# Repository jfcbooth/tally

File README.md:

# Tally
 
A battery-powered seven-segment display counter using a custom PCB. A counter like this can have many unique purposes and can be quickly modified to serve new purpose.

## Resetting the tally
To reset the counter to 0, press either button to wake the device from sleep, then press the small yellow button on the back of the PCB (labelled BTN).

All files necessary to build one for yourself are included in this repository.

<!-- START doctoc generated TOC please keep comment here to allow auto update -->
<!-- DON'T EDIT THIS SECTION, INSTEAD RE-RUN doctoc TO UPDATE -->

- [ATMEGA328 Software](#atmega328-software)
- [PCB](#pcb)
- [Case](#case)

<!-- END doctoc generated TOC please keep comment here to allow auto update -->

## ATMEGA328 Software
1.) Burn Fuses
 - Open arduino software and add the MiniCore library to your board manager:  
 Preferences->Additional Board Manager URLS->paste https://mcudude.github.io/MiniCore/package_MCUdude_MiniCore_index.json  
 - Tools->Board Manager->Search "minicore"->Install  
 - Upload asrduinoISP sketch from arduino software to an arduino uno.  
 - Connect to ATMEGA as shown here:  

| Configured with internal clock | Configured with external clock |
| ----------- | ----------- |
|  |  |

Arduino Flash Options:  
Board->Minicore->ATMEGA328P  
Clock->Internal 1Mhz  
BOD->1.8V  
EEPROM->EEPROM retained  
Compiler LTO->LTO disabled  
Variant->328P/328A  
Bootloader->No bootloader  
PORT-> select your COM port  
Programmer->Arduino as ISP  
Burn bootloader  

Trying configuring the ATMEGA328 with the internal clock first, but if the code doesn't upload, it was probably configured to use an external 16Mhz clock from the factory. You will need a 16Mhz clock which can be de-soldered from an old/dead arduino and 2 22nF capacitors. After burning the bootloader (which sets the fuses), you can remove the crystal and won't need it when uploading sketches from now on. If the code still doesn't upload, make sure all grounds are connected and the supplied voltage is >3V.

2.) Upload Sketch  
 - Open arduino sketch in src  
 - Upload as programmer  (shift click on upload button)

3.) Install ATMEGA328P into PCB  (Note the orientation)

## PCB
| Hardware | Quantity | Purchase location |
| -----------  | -----------  | -----------  |
| ATMEGA328P-PU | 1 | [mouser](https://www.mouser.com/ProductDetail/556-ATMEGA328P-PU) |
| TDCR1050M | 1 | [mouser](https://www.mouser.com/ProductDetail/78-TDCR1050M) |
| C0402C103K5RAC7411 | 4 | [mouser](https://www.mouser.com/ProductDetail/80-C0402C103K5R7411) |
| TPS7A0520PDBZR | 1 | [mouser](https://www.mouser.com/ProductDetail/595-TPS7A0520PDBZR) |
| CRCW08054K70FKEAC | 6 | [mouser](https://www.mouser.com/ProductDetail/71-CRCW08054K70FKEAC) |
| 865080440002 | 2 | [mouser](https://www.mouser.com/ProductDetail/710-865080440002) |
| PTS526 SK08 SMTR2 LFS | 1 | [mouser](https://www.mouser.com/ProductDetail/611-PTS526SK08SMTR2L) |
| 2468 | 1 | [mouser](https://www.mouser.com/ProductDetail/534-2468) |
| Cherry MX Switch Blue | 2 | [amazon](https://www.amazon.com/Cherry-switches-MX1AG1NN-Mechanical-Keyboard/dp/B07RQTNS58/ref=sr_1_3?dchild=1&keywords=cherry+mx+blue+switch&qid=1633447512&sr=8-3) |

I ordered my PCB's through JLCPCB.  
If ordering through them, you can just upload the tally_cam_data.zip zip file in the schematics folder to their website.  
I was supposed to be able to make this design at my university, but none of my professors know how to use the lab eqipment, so I had to order them through a 3rd party. Go Raiders!  

1.) Solder components to PCB (except cherry mx switches)  
2.) Install battery box first by sliding it into place  
3.) Screw PCB into place  
4.) Install Cherry MX switches and solder them to the board  

## Case
For the case, orient it standing tall with the cherry mx switches toward the top.  
It needs printed with a .2mm nozzle for the front lettering to print properly.  
The case is 3d printed, for the back plate, print it laying flat.

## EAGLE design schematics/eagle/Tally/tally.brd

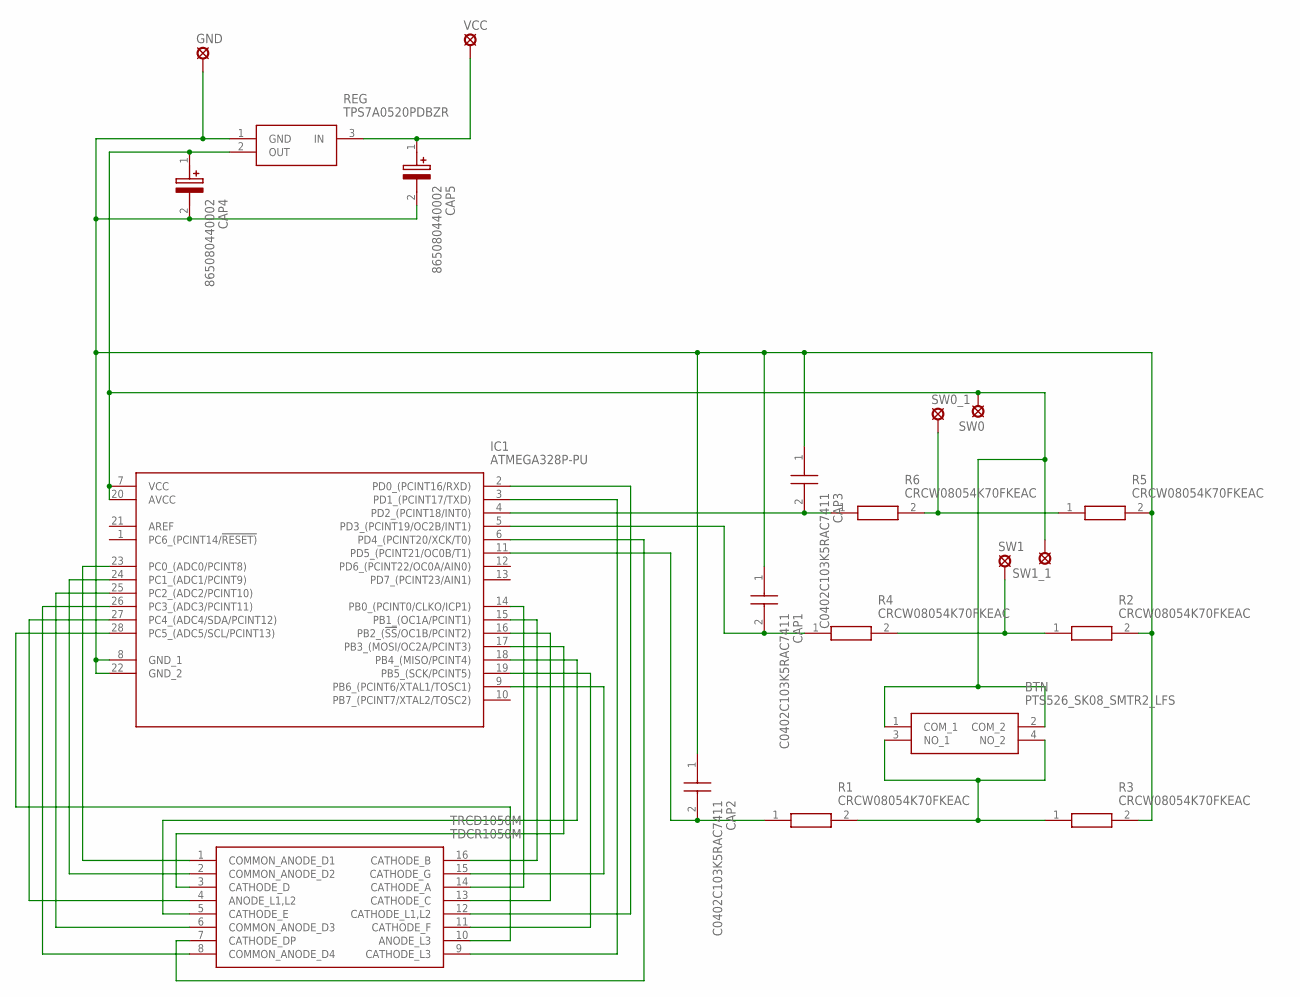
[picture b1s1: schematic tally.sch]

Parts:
BTN: PTS526_SK08_SMTR2_LFS; PTS526SKG15SMTR2LFS
CAP1, CAP2, CAP3: C0402C103K5RAC7411; CAPC1005X55N
CAP4, CAP5: 865080440002; CAPAE400X550N
GND: LSP11
IC1: ATMEGA328P-PU; DIP794W53P254L3467H457Q28N
R1, R2, R3, R4, R5, R6: CRCW08054K70FKEAC; RESC2012X60N
REG: TPS7A0520PDBZR; SOT95P237X112-3N
SW0, SW0_1, SW1, SW1_1: LSP11
TRCD1050M: TDCR1050M; DIPS1016W50P254L4020H725Q16N
VCC: LSP11

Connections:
unnamed: CAP1.1, CAP2.1, CAP3.1, CAP4.2 (-), CAP5.2 (-), GND.MP, IC1.8 (GND_1), IC1.22 (GND_2), R2.2, R3.2, R5.2, REG.1 (GND)
unnamed: CAP5.1 (+), REG.3 (IN), VCC.MP
unnamed: IC1.14 (PB0_(PCINT0/CLKO/ICP1)), TRCD1050M.14 (CATHODE_A)
unnamed: IC1.15 (PB1_(OC1A/PCINT1)), TRCD1050M.16 (CATHODE_B)
unnamed: IC1.16 (PB2_(!SS!/OC1B/PCINT2)), TRCD1050M.13 (CATHODE_C)
unnamed: IC1.17 (PB3_(MOSI/OC2A/PCINT3)), TRCD1050M.3 (CATHODE_D)
unnamed: IC1.18 (PB4_(MISO/PCINT4)), TRCD1050M.5 (CATHODE_E)
unnamed: IC1.19 (PB5_(SCK/PCINT5)), TRCD1050M.11 (CATHODE_F)
unnamed: IC1.9 (PB6_(PCINT6/XTAL1/TOSC1)), TRCD1050M.15 (CATHODE_G)
unnamed: IC1.23 (PC0_(ADC0/PCINT8)), TRCD1050M.1 (COMMON_ANODE_D1)
unnamed: IC1.24 (PC1_(ADC1/PCINT9)), TRCD1050M.2 (COMMON_ANODE_D2)
unnamed: IC1.25 (PC2_(ADC2/PCINT10)), TRCD1050M.6 (COMMON_ANODE_D3)
unnamed: IC1.26 (PC3_(ADC3/PCINT11)), TRCD1050M.8 (COMMON_ANODE_D4)
unnamed: IC1.27 (PC4_(ADC4/SDA/PCINT12)), TRCD1050M.4 (ANODE_L1,L2)
unnamed: IC1.28 (PC5_(ADC5/SCL/PCINT13)), TRCD1050M.10 (ANODE_L3)
unnamed: IC1.2 (PD0_(PCINT16/RXD)), TRCD1050M.12 (CATHODE_L1,L2)
unnamed: IC1.3 (PD1_(PCINT17/TXD)), TRCD1050M.9 (CATHODE_L3)
unnamed: IC1.6 (PD4_(PCINT20/XCK/T0)), TRCD1050M.7 (CATHODE_DP)
unnamed: R5.1, R6.2, SW0_1.MP
unnamed: CAP3.2, IC1.4 (PD2_(PCINT18/INT0)), R6.1
unnamed: CAP1.2, IC1.5 (PD3_(PCINT19/OC2B/INT1)), R4.1
unnamed: R2.1, R4.2, SW1.MP
unnamed: CAP2.2, IC1.11 (PD5_(PCINT21/OC0B/T1)), R1.1
unnamed: BTN.1 (COM_1), BTN.2 (COM_2), CAP4.1 (+), IC1.7 (VCC), IC1.20 (AVCC), REG.2 (OUT), SW0.MP, SW1_1.MP
unnamed: BTN.3 (NO_1), BTN.4 (NO_2), R1.2, R3.1

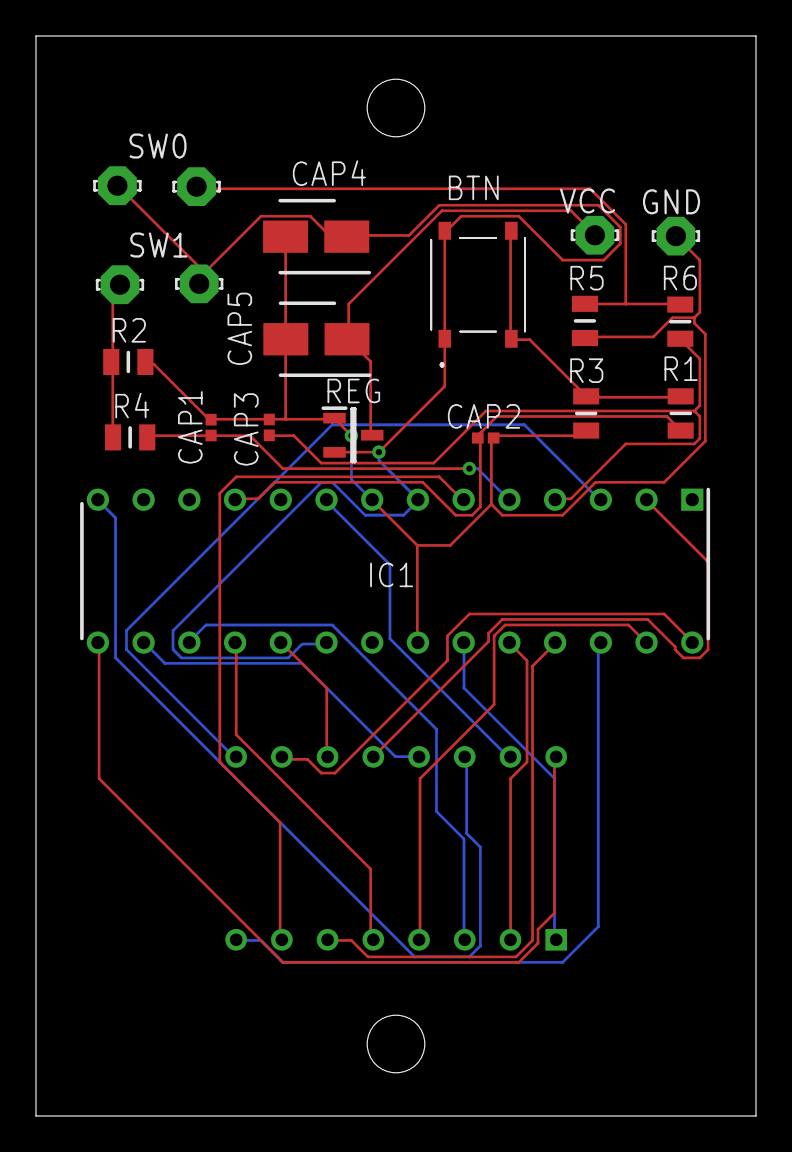
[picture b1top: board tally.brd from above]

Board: 2 copper layers, 40.0 x 60.0 mm, 21 parts (1 on the bottom side), 25 nets.

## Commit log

2021-08-18 multi-digit numebers displaying
2021-08-18 working interrupt
2021-08-19 interrupts and sleep mode
2021-08-19 working version with push buttons
2021-08-20 all features working
2021-08-21 fixed tally overflow and added tally reset directive
2021-10-05 added project files
2021-10-08 scrubbed
2021-10-09 added pictures
